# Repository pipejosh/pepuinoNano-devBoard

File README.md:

# Pepuino Nano V1

This is a develpment board, that is ahead of its time (theres nothing futuristic about it hehe), featuring and amazing design, and a RP2040, custom made from scratch following the diagram from the pico

## Images!!

### Renders

### PCB

### Schematic

### BOM

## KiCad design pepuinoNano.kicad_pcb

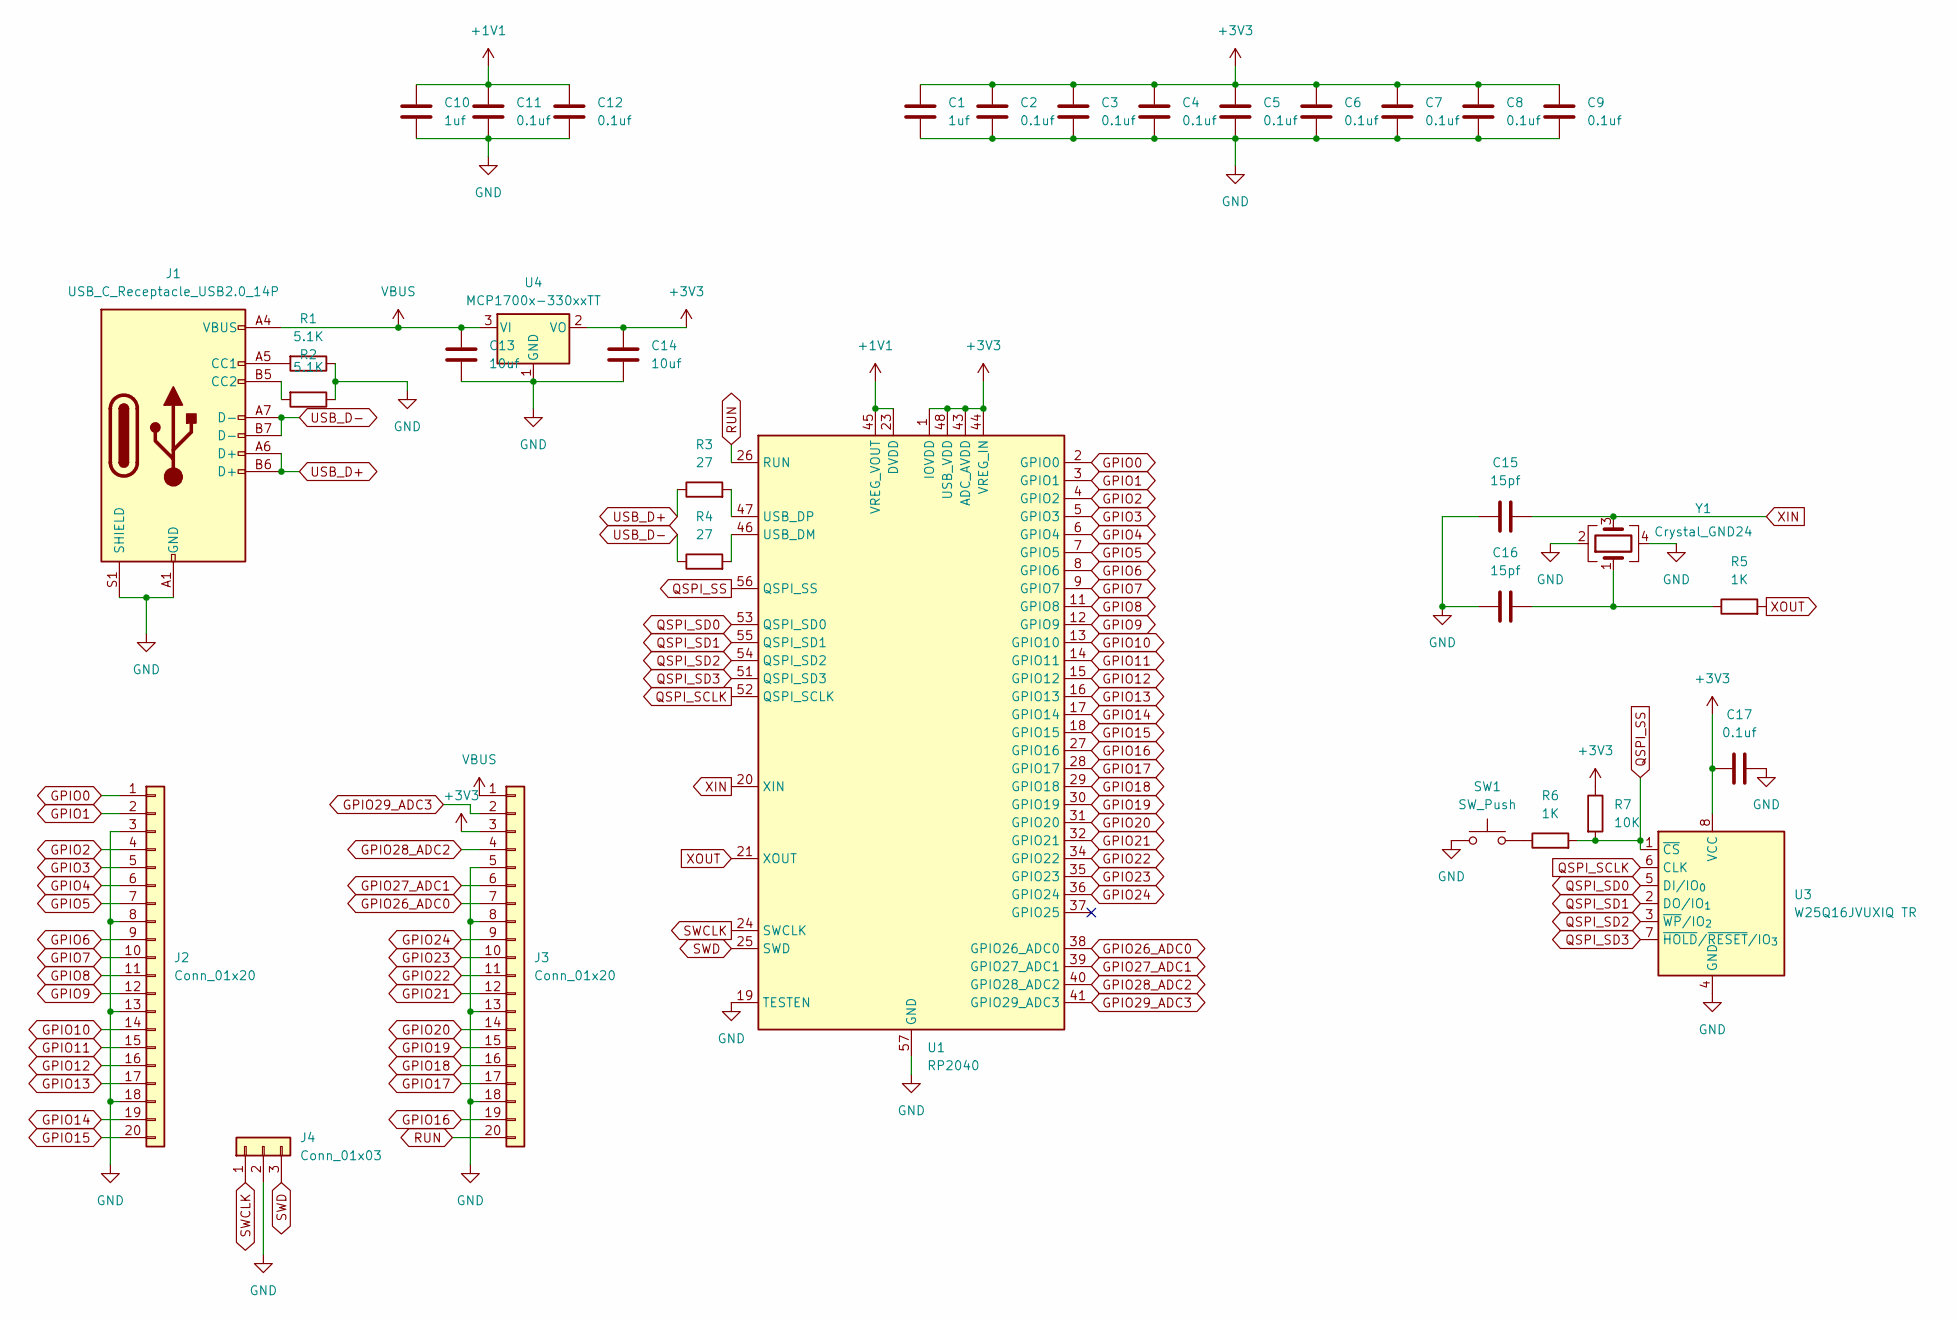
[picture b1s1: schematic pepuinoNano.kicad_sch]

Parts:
C1, C10: 1uf; C_0402_1005Metric
C2, C3, C4, C5, C6, C7, C8, C9, C11, C12, C17: 0.1uf; C_0402_1005Metric
C13, C14: 10uf; C_0402_1005Metric
C15, C16: 15pf; C_0402_1005Metric
J1: USB_C_Receptacle_USB2.0_14P; USB_C_Receptacle_HRO_TYPE-C-31-M-12
J2, J3: Conn_01x20; PinHeader_1x20_P2.54mm_Vertical
J4: Conn_01x03; PinHeader_1x03_P2.54mm_Vertical
R1, R2: 5.1K; R_0402_1005Metric
R3, R4: 27; R_0402_1005Metric
R5, R6: 1K; R_0402_1005Metric
R7: 10K; R_0402_1005Metric
SW1: SW_Push; SW_Push_SPST_NO_Alps_SKRK
U1: RP2040; QFN-56-1EP_7x7mm_P0.4mm_EP3.2x3.2mm
U3: W25Q16JVUXIQ TR; Winbond_USON-8-1EP_3x2mm_P0.5mm_EP0.2x1.6mm
U4: MCP1700x-330xxTT; SOT-23
Y1: Crystal_GND24; Crystal_SMD_3225-4Pin_3.2x2.5mm

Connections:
+1V1: C10.1, C11.1, C12.1, U1.23 (DVDD), U1.45 (VREG_VOUT), U1.50 (DVDD)
+3V3: C1.1, C2.1, C3.1, C4.1, C5.1, C6.1, C7.1, C8.1, C9.1, C14.1, C17.1, J3.3, R7.1, U1.1 (IOVDD), U1.10 (IOVDD), U1.22 (IOVDD), U1.33 (IOVDD), U1.42 (IOVDD), U1.43 (ADC_AVDD), U1.44 (VREG_IN), U1.48 (USB_VDD), U1.49 (IOVDD), U3.8 (VCC), U4.2 (VO)
GND: C1.2, C2.2, C3.2, C4.2, C5.2, C6.2, C7.2, C8.2, C9.2, C10.2, C11.2, C12.2, C13.2, C14.2, C15.1, C16.1, C17.2, J1.A1 (GND), J1.A12 (GND), J1.B1 (GND), J1.B12 (GND), J1.S1 (SHIELD), J2.3, J2.8, J2.13, J2.18, J3.5, J3.8, J3.13, J3.18, J4.2, R1.1, R2.1, SW1.1, U1.19 (TESTEN), U1.57 (GND), U3.4 (GND), U4.1 (GND), Y1.2, Y1.4
GPIO0: J2.1, U1.2 (GPIO0)
GPIO1: J2.2, U1.3 (GPIO1)
GPIO2: J2.4, U1.4 (GPIO2)
GPIO3: J2.5, U1.5 (GPIO3)
GPIO4: J2.6, U1.6 (GPIO4)
GPIO5: J2.7, U1.7 (GPIO5)
GPIO6: J2.9, U1.8 (GPIO6)
GPIO7: J2.10, U1.9 (GPIO7)
GPIO8: J2.11, U1.11 (GPIO8)
GPIO9: J2.12, U1.12 (GPIO9)
GPIO10: J2.14, U1.13 (GPIO10)
GPIO11: J2.15, U1.14 (GPIO11)
GPIO12: J2.16, U1.15 (GPIO12)
GPIO13: J2.17, U1.16 (GPIO13)
GPIO14: J2.19, U1.17 (GPIO14)
GPIO15: J2.20, U1.18 (GPIO15)
GPIO16: J3.19, U1.27 (GPIO16)
GPIO17: J3.17, U1.28 (GPIO17)
GPIO18: J3.16, U1.29 (GPIO18)
GPIO19: J3.15, U1.30 (GPIO19)
GPIO20: J3.14, U1.31 (GPIO20)
GPIO21: J3.12, U1.32 (GPIO21)
GPIO22: J3.11, U1.34 (GPIO22)
GPIO23: J3.10, U1.35 (GPIO23)
GPIO24: J3.9, U1.36 (GPIO24)
GPIO26_ADC0: J3.7, U1.38 (GPIO26_ADC0)
GPIO27_ADC1: J3.6, U1.39 (GPIO27_ADC1)
GPIO28_ADC2: J3.4, U1.40 (GPIO28_ADC2)
GPIO29_ADC3: J3.2, U1.41 (GPIO29_ADC3)
unnamed: C16.2, R5.1, Y1.1
unnamed: J1.A5 (CC1), R1.2
unnamed: J1.B5 (CC2), R2.2
unnamed: R6.1, SW1.2
unnamed: R4.2, U1.46 (USB_DM)
unnamed: R3.2, U1.47 (USB_DP)
QSPI_SCLK: U1.52 (QSPI_SCLK), U3.6 (CLK)
QSPI_SD0: U1.53 (QSPI_SD0), U3.5 (DI/IO_{0})
QSPI_SD1: U1.55 (QSPI_SD1), U3.2 (DO/IO_{1})
QSPI_SD2: U1.54 (QSPI_SD2), U3.3 (~WP/IO_{2})
QSPI_SD3: U1.51 (QSPI_SD3), U3.7 (~HOLD/~RESET/IO_{3})
QSPI_SS: R6.2, R7.2, U1.56 (QSPI_SS), U3.1 (~CS)
RUN: J3.20, U1.26 (RUN)
SWCLK: J4.1, U1.24 (SWCLK)
SWD: J4.3, U1.25 (SWD)
USB_D+: J1.A6 (D+), J1.B6 (D+), R3.1
USB_D-: J1.A7 (D-), J1.B7 (D-), R4.1
VBUS: C13.1, J1.A4 (VBUS), J1.A9 (VBUS), J1.B4 (VBUS), J1.B9 (VBUS), J3.1, U4.3 (VI)
XIN: C15.2, U1.20 (XIN), Y1.3
XOUT: R5.2, U1.21 (XOUT)

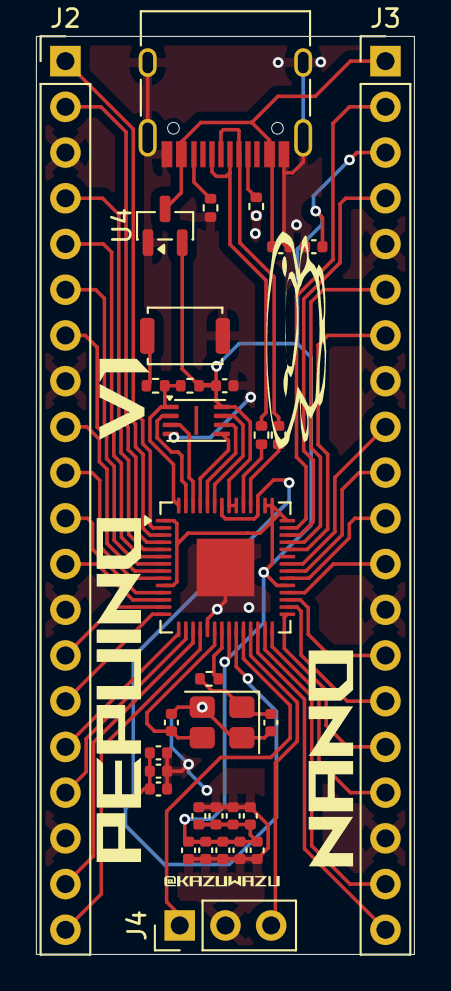
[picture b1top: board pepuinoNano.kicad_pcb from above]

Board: 2 copper layers, 21.0 x 51.0 mm, 33 parts (0 on the bottom side), 52 nets.

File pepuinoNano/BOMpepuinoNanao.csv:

"Reference","Qty","Value","DNP","Exclude from BOM","Exclude from Board","Footprint","Datasheet"
"C1,C10","2","1uf","","","","Capacitor_SMD:C_0402_1005Metric","~"
"C2,C3,C4,C5,C6,C7,C8,C9,C11,C12,C17","11","0.1uf","","","","Capacitor_SMD:C_0402_1005Metric","~"
"C13,C14","2","10uf","","","","Capacitor_SMD:C_0402_1005Metric","~"
"C15,C16","2","15pf","","","","Capacitor_SMD:C_0402_1005Metric","~"
"J1","1","USB_C_Receptacle_USB2.0_14P","","","","Connector_USB:USB_C_Receptacle_HRO_TYPE-C-31-M-12","https://www.usb.org/sites/default/files/documents/usb_type-c.zip"
"J2,J3","2","Conn_01x20","","","","Connector_PinHeader_2.54mm:PinHeader_1x20_P2.54mm_Vertical","~"
"J4","1","Conn_01x03","","","","Connector_PinHeader_2.54mm:PinHeader_1x03_P2.54mm_Vertical","~"
"R1,R2","2","5.1K","","","","Resistor_SMD:R_0402_1005Metric","~"
"R3,R4","2","27","","","","Resistor_SMD:R_0402_1005Metric","~"
"R5,R6","2","1K","","","","Resistor_SMD:R_0402_1005Metric","~"
"R7","1","10K","","","","Resistor_SMD:R_0402_1005Metric","~"
"SW1","1","SW_Push","","","","Button_Switch_SMD:SW_Push_SPST_NO_Alps_SKRK","~"
"U1","1","RP2040","","","","Package_DFN_QFN:QFN-56-1EP_7x7mm_P0.4mm_EP3.2x3.2mm","https://datasheets.raspberrypi.com/rp2040/rp2040-datasheet.pdf"
"U3","1","W25Q16JVZPIQ","","","","Package_SON:Winbond_USON-8-1EP_3x2mm_P0.5mm_EP0.2x1.6mm","https://www.winbond.com/resource-files/w25q128jv_dtr%20revc%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"
"U4","1","MCP1700x-330xxTT","","","","Package_TO_SOT_SMD:SOT-23","http://ww1.microchip.com/downloads/en/DeviceDoc/20001826D.pdf"
"Y1","1","Crystal_GND24","","","","Crystal:Crystal_SMD_3225-4Pin_3.2x2.5mm","~"

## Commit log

2025-12-28 add readme.md + images
2025-12-28 start from scratch
2025-12-28 initial commit part 2
2026-01-30 update the resistor r3 and r4 from 27k to 27
2026-01-30 update readme.md plus update pictures!
2026-01-30 Fix typos and improve README content
